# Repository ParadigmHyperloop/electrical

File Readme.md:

# Electrical System for the Paradigm Hyperloop Pod

## Quick Start

All boards are built using KiCad EDA (http://kicad.org/).  It is free and open source software!

1. Download and Install KiCAD
2. Clone this Repo
3. Checkout a new branch or your branch other than master
3. Open the project file (.pro) for the board you are interested in
4. Make any edits, create a branch, add and commit the changes to git, then push. 

## Organization

All files for the current revision should be kept in folders in the root directory.
All files for a completed revision should be kept in folders in the appropriate "RevX" sub-directory.
Still not sure how we will handle when some boards need to be revved but not others...

## Ops Roadmap

There are a number of nice-to-have features that will streamline the electrical workflow of board
design. The following features employ a CI server that minicks some of the features that the software
team enjoys in their git workflow.

- Automatic DRC when the PR is opened. Gate PRs on passing DRC.
- Whenever A new PR is merged to `master`, a bot will pull `master` and do the following, and commit the changes back to `master`
  - Automatic PDF export and storage in `./<board>/PDFs/`
  - Automatic BOM export and storage as `./<board>/BOM.csv`
  - Automatic SVG export and storage in `./<board>/SVG/`
  - Automatic 3D Viewer export and storage in `./<board>/3D/`
  - Automatic DRC report and storage in `./<board>/reports/`
  - Automatic export of gerbers and drill files per spec file.  Storage in `./<board>/mfg/`
  - Automatic Generation of `./board/BOT.version` containing the SHA of the commit that everything was generated for 

# License

See the [LICENSE](LICENSE) for full licensing details.

In summary, (you still need to read the whole thing), these boards are for Paradigm, 
and Paradigm only. It is shared with the world for the benefit of observers and 
potential Paradigm team members. If you wish to utilize these designs in any
way, you must contact us first and receive written permission to utilize the
designs for the purpose you require. 

We don't want to be restrictive, and we will almost certainly grant you permission,
but we want to know what you are using our designs for, and we want to make sure
you are using them correctly and safely.

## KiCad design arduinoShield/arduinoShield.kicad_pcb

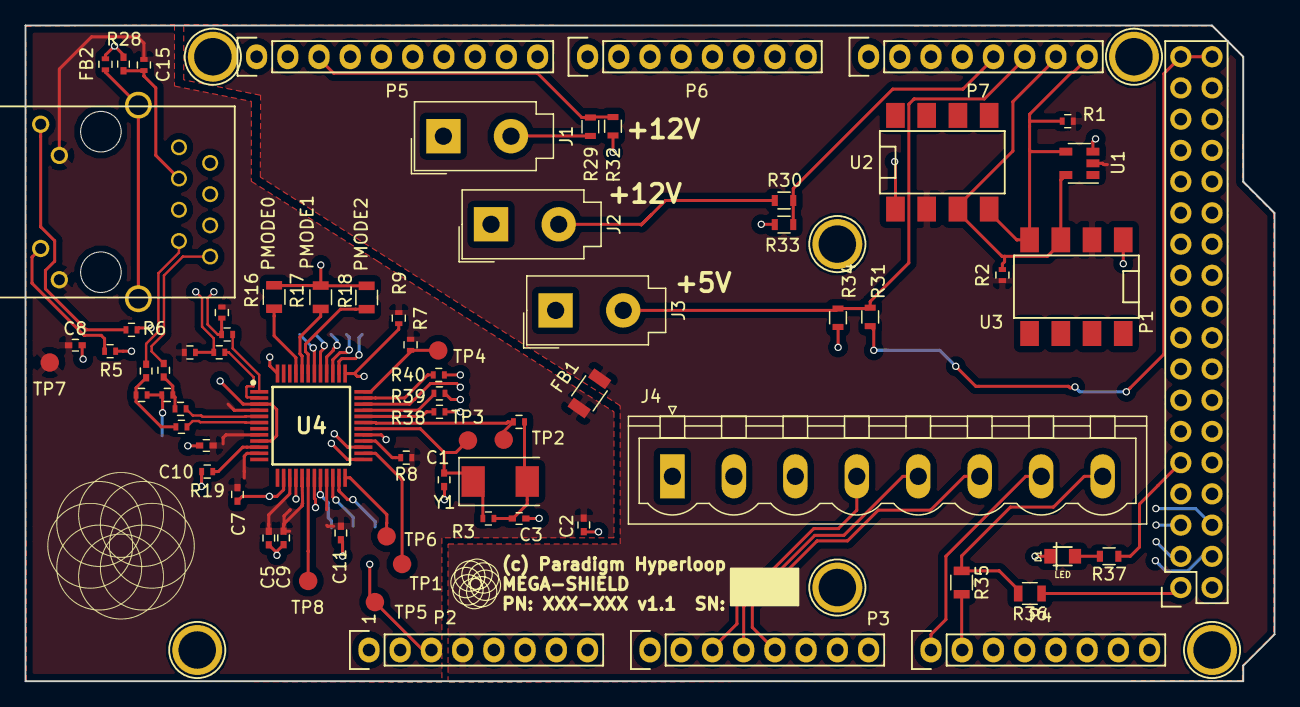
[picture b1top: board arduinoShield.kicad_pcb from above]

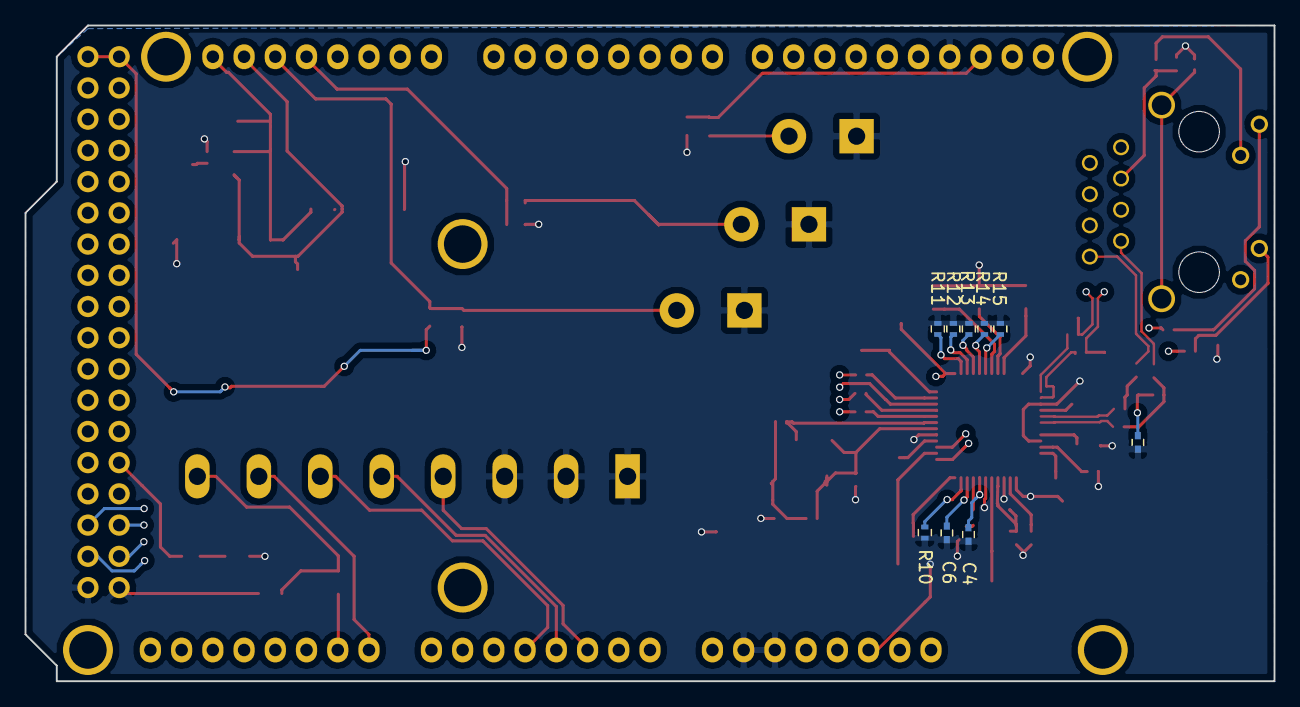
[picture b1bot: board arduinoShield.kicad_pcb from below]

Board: 4 copper layers, 101.6 x 53.3 mm, 91 parts (9 on the bottom side), 64 nets.

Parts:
C1, C3, C4: 4.7uF; C_0402
C2: 10uF; C_0402
C5, C7, C8, C9, C10, C11: 0.1uF; C_0402
C6, C12: 10nF; C_0402
C13, C14: 6.8nF; C_0402
C15: 100nF; C_0402
D1: LED; LED_Wurth_WL-SMCW_0805_B
FB1: Ferrite_Bead_Small; R_1206
FB2: Ferrite_Bead_Small; R_0402
J1, J2, J3: Screw_Terminal_01x02; Molex_MiniFit-JR-5556-02A_2x01x4.20mm_Straight
J4: ADC; PhoenixContact_MSTBVA-G_08x5.00mm_Vertical
P1: Digital; Socket_Strip_Arduino_2x18
P2: Power; Socket_Strip_Arduino_1x08
P3, P4: Analog; Socket_Strip_Arduino_1x08
P5: PWM; Socket_Strip_Arduino_1x10
P6: PWM; Socket_Strip_Arduino_1x08
P7: Communication; Socket_Strip_Arduino_1x08
P8, P9, P10, P11, P12, P13: CONN_01X01; Arduino_1pin
P14: RB1-125BAG1A; WIZNET_RB1-125BAG1A
R1, R2: 4K7; R_0402
R3: 1M; R_0402
R4, R8, R38, R39, R40: 0; R_0402
R5, R6: 330; R_0402
R7, R9, R10, R11, R12, R13, R14, R15: 10k; R_0402
R16, R17, R18, R35, R36: 10k; R_0805
R19: 12.4k; R_0402
R20, R21, R23, R24: 33; R_0402
R22, R25, R26, R27, R28: 49.9; R_0402
R29, R30: 14k; R_0603
R31: 300; R_0603
R32, R33, R34: 10k; R_0603
R37: 1k; R_0603
TP1, TP2, TP3, TP4, TP5, TP6, TP8: Measurement_Point_Round-SMD-Pad_Small
TP7: TestPoint; Measurement_Point_Round-SMD-Pad_Small
U1: TC74; SOT-23-5
U2, U3: HSCDANN030PA2A3; DIP-8_SMD
U4: W5500; QFP50P900X900X160-48N
Y1: 25MHz; Crystal_SMD_0603-2pin_6.0x3.5mm
logo1: Logo; Paradigm_Logo_Very_Small
logo2: Logo; SN_BLOCK

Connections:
3V3_WIZ: C2.1, C5.1, C7.1, C8.1, C9.1, C10.1, C11.1, FB1.2, P14.L1, P14.L3, R7.1, R8.1, R9.1, R26.1, R27.1, R28.2, TP7.1, U4.4, U4.8, U4.11, U4.15, U4.17, U4.21
+3V3: FB1.1, P2.4, R1.1, R2.1, U1.2, U2.2, U3.2
+5V: P1.35, P1.36, R31.2
/18(Tx1): P7.5, R30.1, R33.1
/19(Rx1): J3.2, P7.6, R31.1, R34.1
/20(SDA): P7.7, R2.2, U1.5, U2.3, U3.3
/21(SCL): P7.8, R1.2, U1.4, U2.4, U3.4
/46: P1.9, R37.1
/A2: J4.4, P3.3
/A3: J4.5, P3.4
/A4: J4.6, P3.5
/A8: J4.7, P4.1
/A9: P4.2, R35.2
/AREF: P5.3, R29.1, R32.1
/wiznet/1V2_VGB_NC: TP8.1, U4.18
/wiznet/1V20: C6.1, U4.22
/wiznet/ACT_LED: R6.1, U4.27
/wiznet/ACT_LED_R: P14.L4, R6.2
/wiznet/DUP_LED_NC: TP1.1, U4.26
/wiznet/LINK_LED: R5.1, U4.25
/wiznet/LINK_LED_R: P14.L2, R5.2
/wiznet/NETW_S0: R38.1, U4.32
/wiznet/NETW_S1: R39.1, U4.33
/wiznet/NETW_S3: R40.1, U4.35
/wiznet/PMODE0: R16.2, U4.45
/wiznet/PMODE1: R17.2, U4.44
/wiznet/PMODE2: R18.2, U4.43
/wiznet/REF_CAP: C4.1, U4.20
/wiznet/RSVD0: R10.1, U4.23
/wiznet/RSVD1: R11.1, U4.38
/wiznet/RSVD2: R12.1, U4.39
/wiznet/RSVD3: R13.1, U4.40
/wiznet/RSVD4: R14.1, U4.41
/wiznet/RSVD5: R15.1, U4.42
/wiznet/RX_C_N: C14.1, P14.R8
/wiznet/RX_C_P: C13.1, P14.R7
/wiznet/RX_N: R20.2, U4.5
/wiznet/RX_P: R21.2, U4.6
/wiznet/SPD_LED_NC: TP6.1, U4.24
/wiznet/TX_N: R24.2, U4.1
/wiznet/TX_P: R23.2, U4.2
/wiznet/TX_R_N: P14.R2, R24.1, R27.2
/wiznet/TX_R_P: P14.R1, R23.1, R26.2
GND: C1.2, C2.2, C3.2, C4.2, C5.2, C6.2, C7.2, C8.2, C9.2, C10.2, C11.2, C12.1, C15.1, D1.1, FB2.2, J1.1, J2.1, J3.1, J4.1, J4.2, J4.3, P1.1, P1.2, P2.6, P2.7, P5.4, R10.2, R11.2, R12.2, R13.2, R14.2, R15.2, R16.1, R17.1, R18.1, R19.2, R32.2, R33.2, R34.2, R36.1, U1.3, U2.1, U3.1, U4.3, U4.9, U4.14, U4.16, U4.19, U4.29, U4.48
NETW_INT_L: R7.2, TP4.1, U4.36
NETW_MISO: P1.5, U4.34
NETW_MOSI: P1.6, R40.2
NETW_RST_L: P2.3, R9.2, TP5.1, U4.37
NETW_SCLK: P1.3, R39.2
NETW_SS: P1.4, R38.2
unnamed: C1.1, R3.2, TP3.1, U4.30, Y1.1
unnamed: C3.1, R3.1, R4.2, Y1.2
unnamed: C12.2, R22.2, R25.2
unnamed: C13.2, R21.1, R22.1
unnamed: C14.2, R20.1, R25.1
unnamed: C15.2, P14.R3, R28.1
unnamed: D1.2, R37.2
unnamed: FB2.1, P14.SH
unnamed: J1.2, R29.2
unnamed: J2.2, R30.2
unnamed: J4.8, R35.1, R36.2
unnamed: R4.1, TP2.1, U4.31
unnamed: R8.2, U4.28
unnamed: R19.1, U4.10

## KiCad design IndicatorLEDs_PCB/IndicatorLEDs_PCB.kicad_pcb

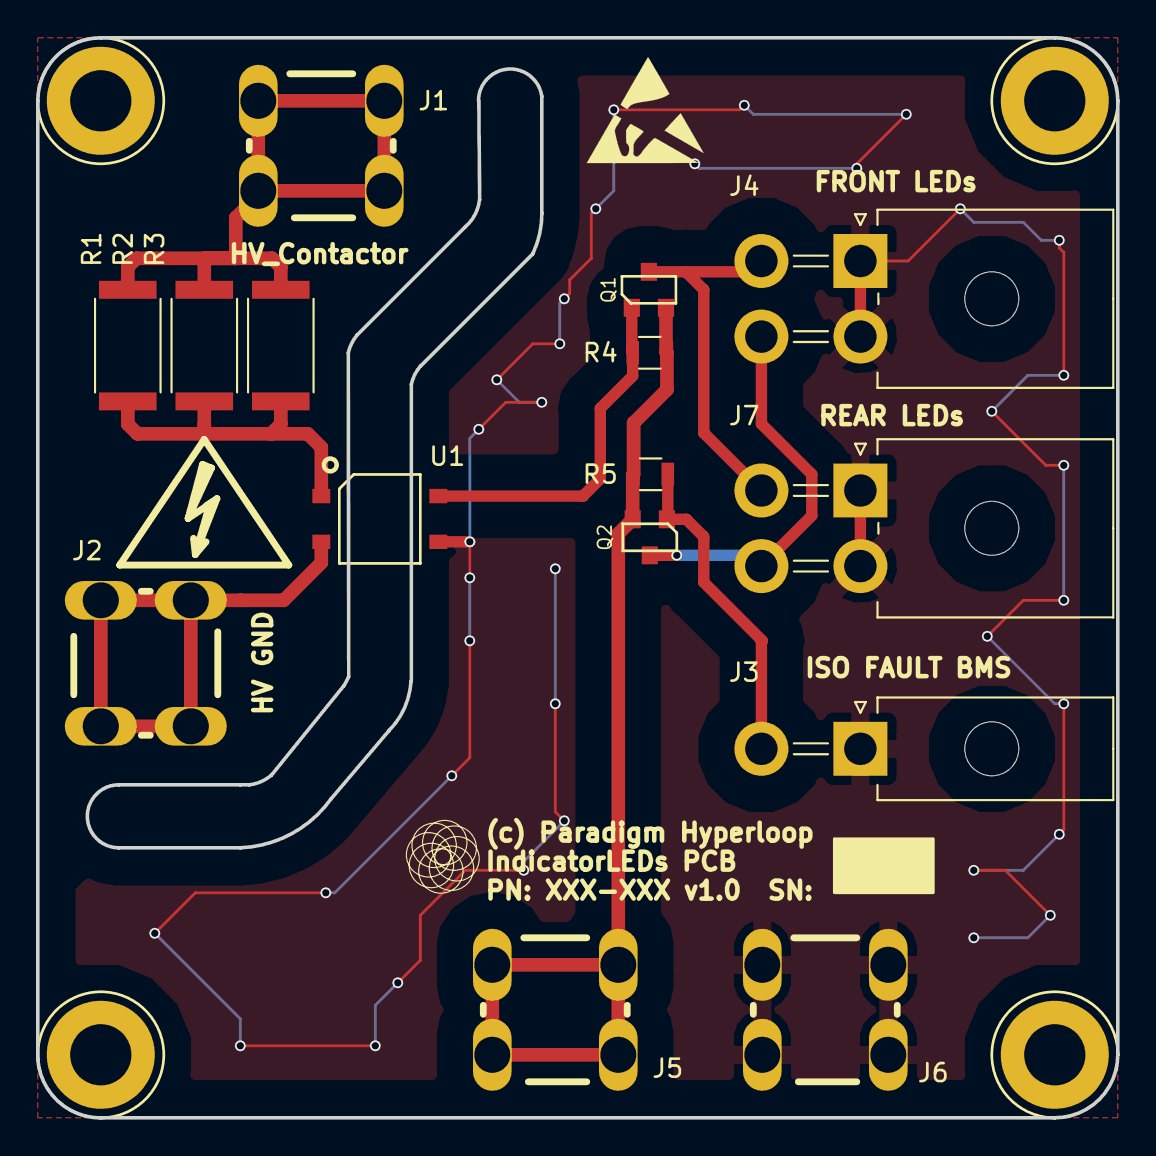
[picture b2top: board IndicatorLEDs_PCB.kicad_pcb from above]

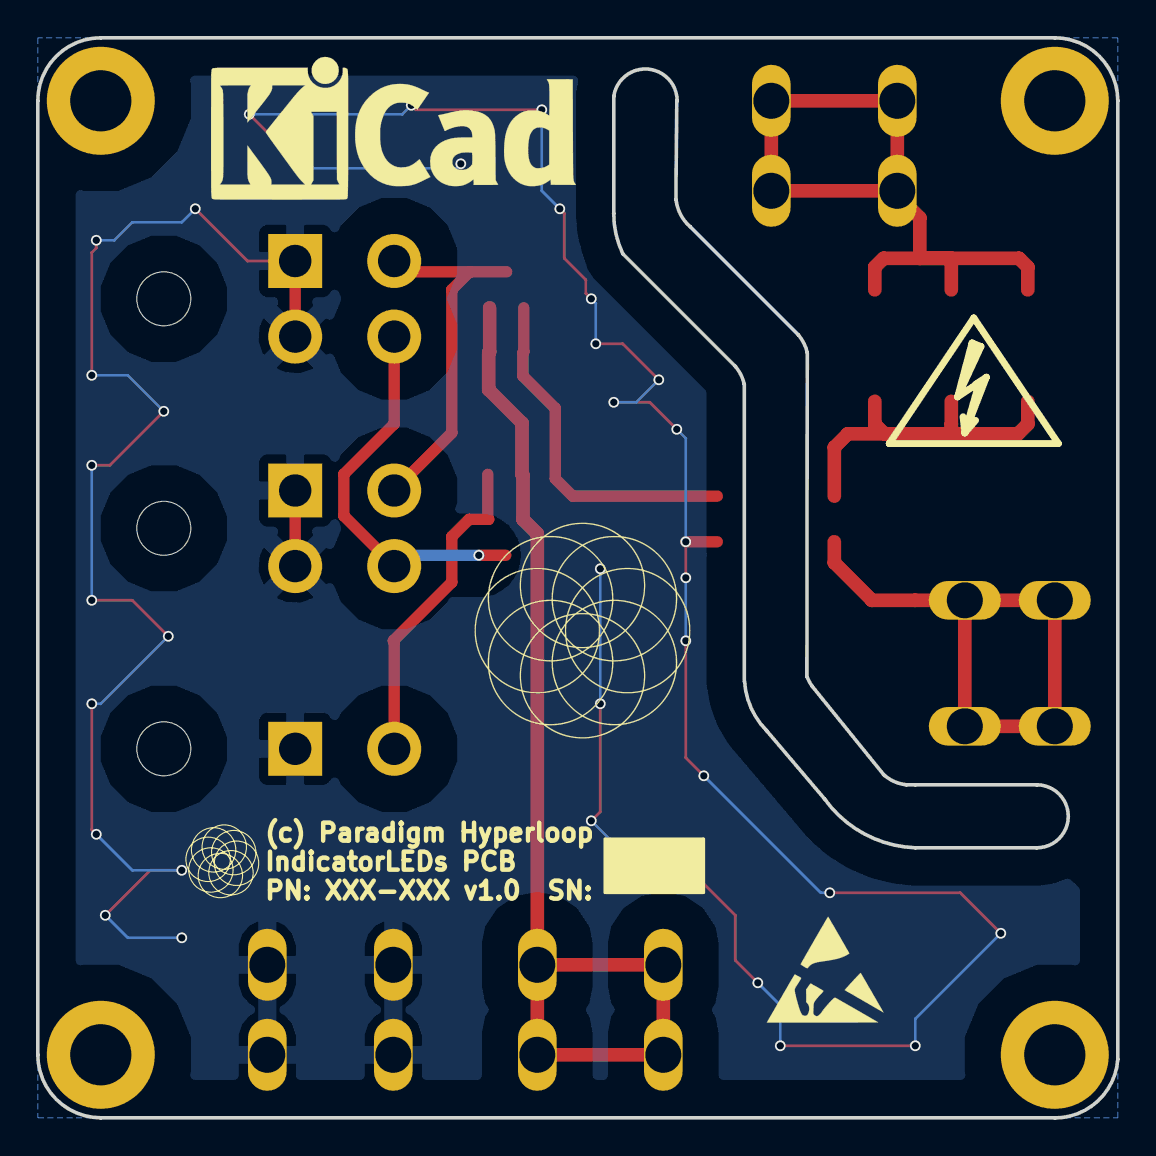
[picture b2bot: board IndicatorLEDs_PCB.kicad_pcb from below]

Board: 2 copper layers, 60.0 x 60.0 mm, 29 parts (6 on the bottom side), 9 nets.

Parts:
H1, H2, H3, H4: Mount; 3.4mm_mounting_hole_SILK
J1, J2, J5, J6: M3 LUG; LVDC_M3_Lug
J3: BMS_I; Molex_MiniFit-JR-5569-02A2_2x01x4.20mm_Angled
J4: FRNT_LEDs; Molex_MiniFit-JR-5569-04A2_2x02x4.20mm_Angled
J7: REAR_LEDs; Molex_MiniFit-JR-5569-04A2_2x02x4.20mm_Angled
Q1, Q2: Q_PMOS_GSD; SOT-23-3
R1, R2, R3: 1M; R_2512
R4, R5: 10k; R_0805
U1: LTV-357; Optocoupler_SOIC-4_LTV-357
logo1, logo1#2: SN_Block; SN_BLOCK
logo2: Logo; ParadigmLogo_0_5x0_5
logo3, logo3#2: Logo; Paradigm_Logo_Very_Small
logo4, logo6: Logo; ESD-Logo_6.6x6mm_SilkScreen
logo5, logo8: Logo; Symbol_HighVoltage_Type2_SilkTop_VerySmall
logo7: Logo; KiCad-Logo_8mm_SilkScreen

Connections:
+12V: J5.1, Q1.2, Q2.2, R4.1, R5.1
/BMS_Shorted_I: J3.2, Q2.1, R5.2
/GREEN_LED_FRONT: J4.4, J7.4, Q2.3
/HV_Connected: Q1.1, R4.2, U1.4
/HV_Contactor_+: J1.1, R1.2, R2.2, R3.2
/RED_LED_FRONT: J4.3, J7.3, Q1.3
GND: J3.1, J4.1, J4.2, J6.1, J7.1, J7.2, U1.3
ISO_GND: J2.1, U1.2
unnamed: R1.1, R2.1, R3.1, U1.1
